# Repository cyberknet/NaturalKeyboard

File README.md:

# NaturalKeyboard
Custom Mechanical Keyboard PCB that will eventually have a Natural/Ergonomic layout. Never had PCBs fabricated, please reference or use at your own risk.

## Schematic

## PCB Front

## PCB Reverse

## Render Front

## Render Reverse

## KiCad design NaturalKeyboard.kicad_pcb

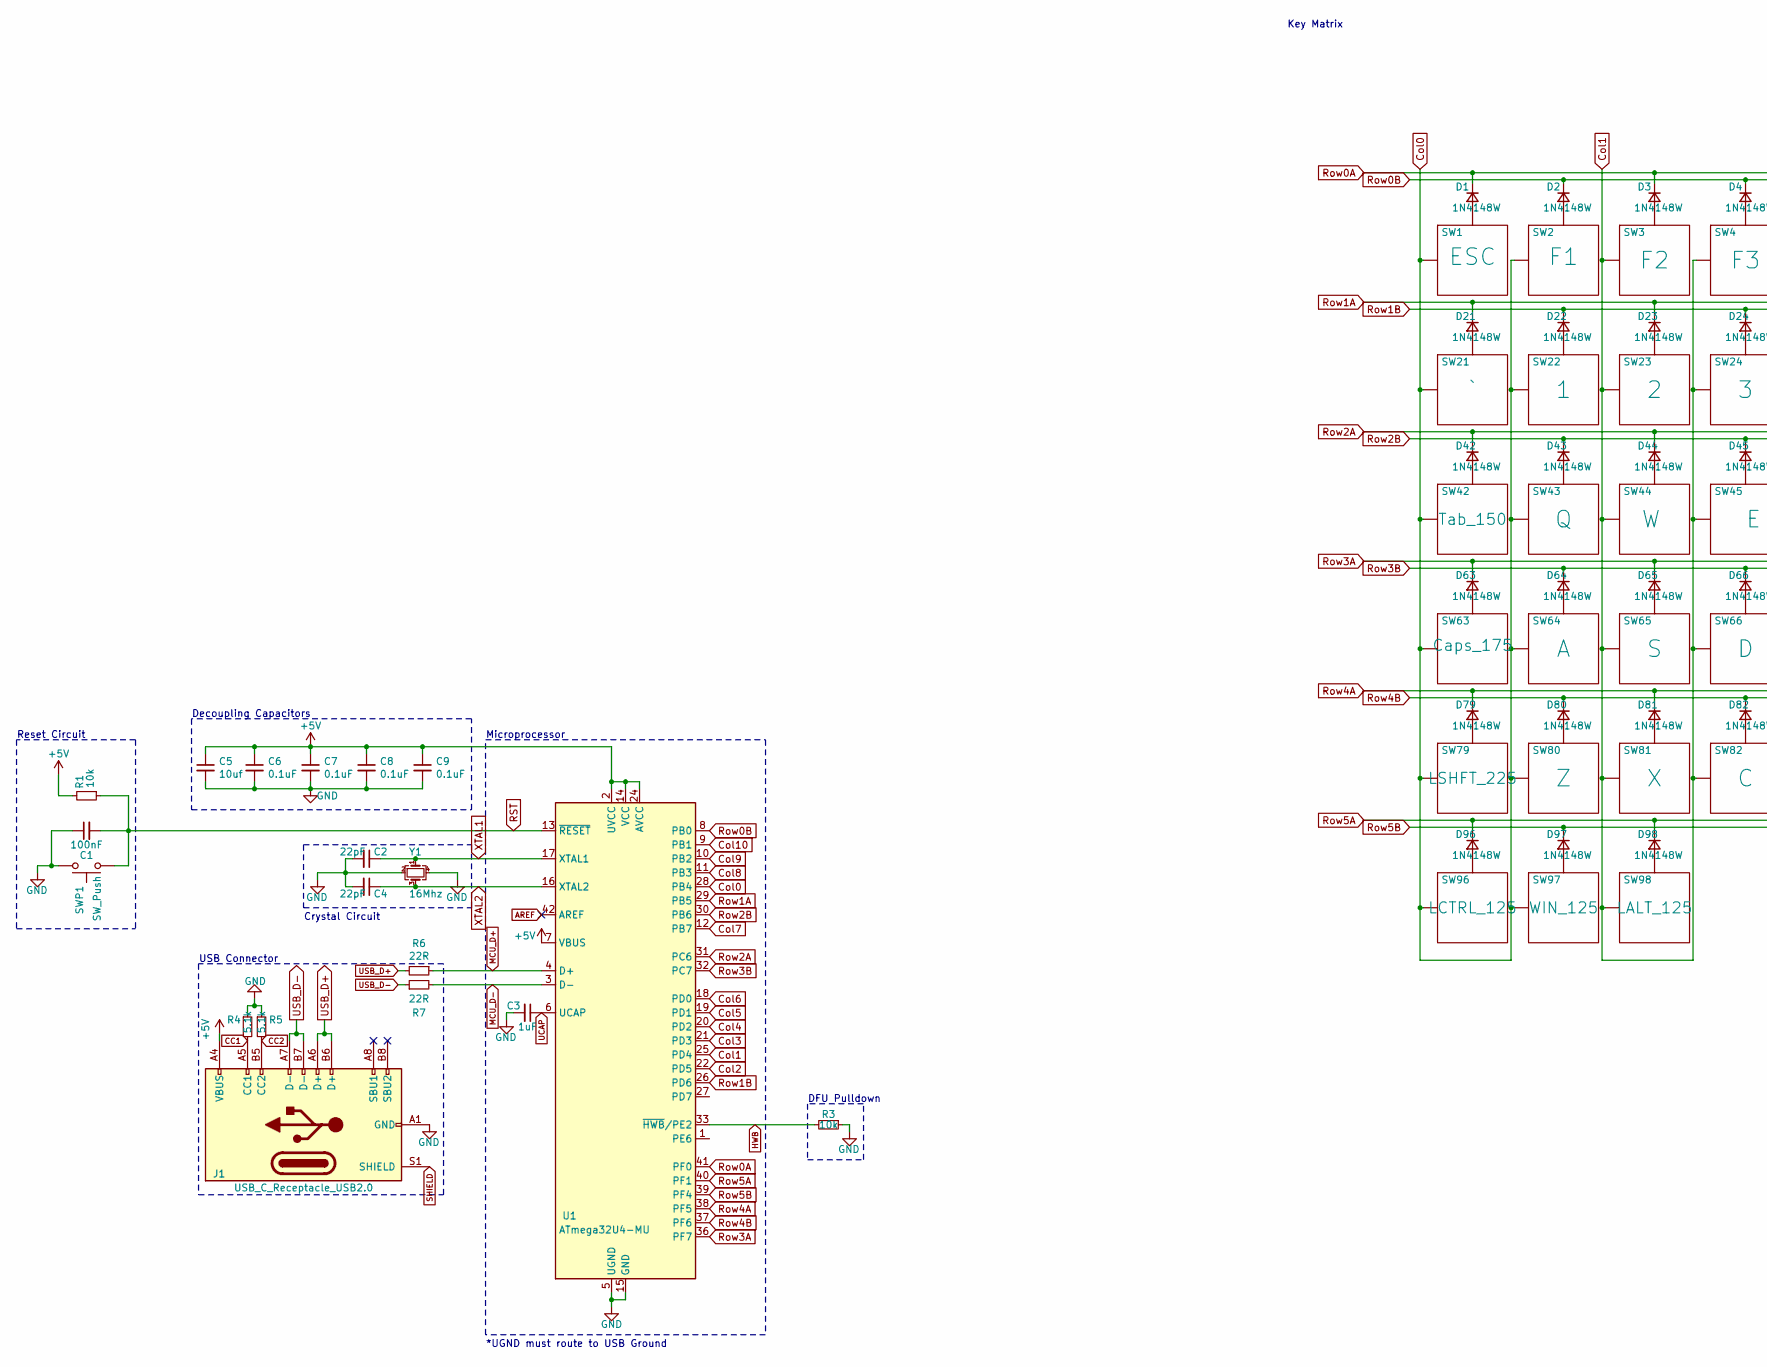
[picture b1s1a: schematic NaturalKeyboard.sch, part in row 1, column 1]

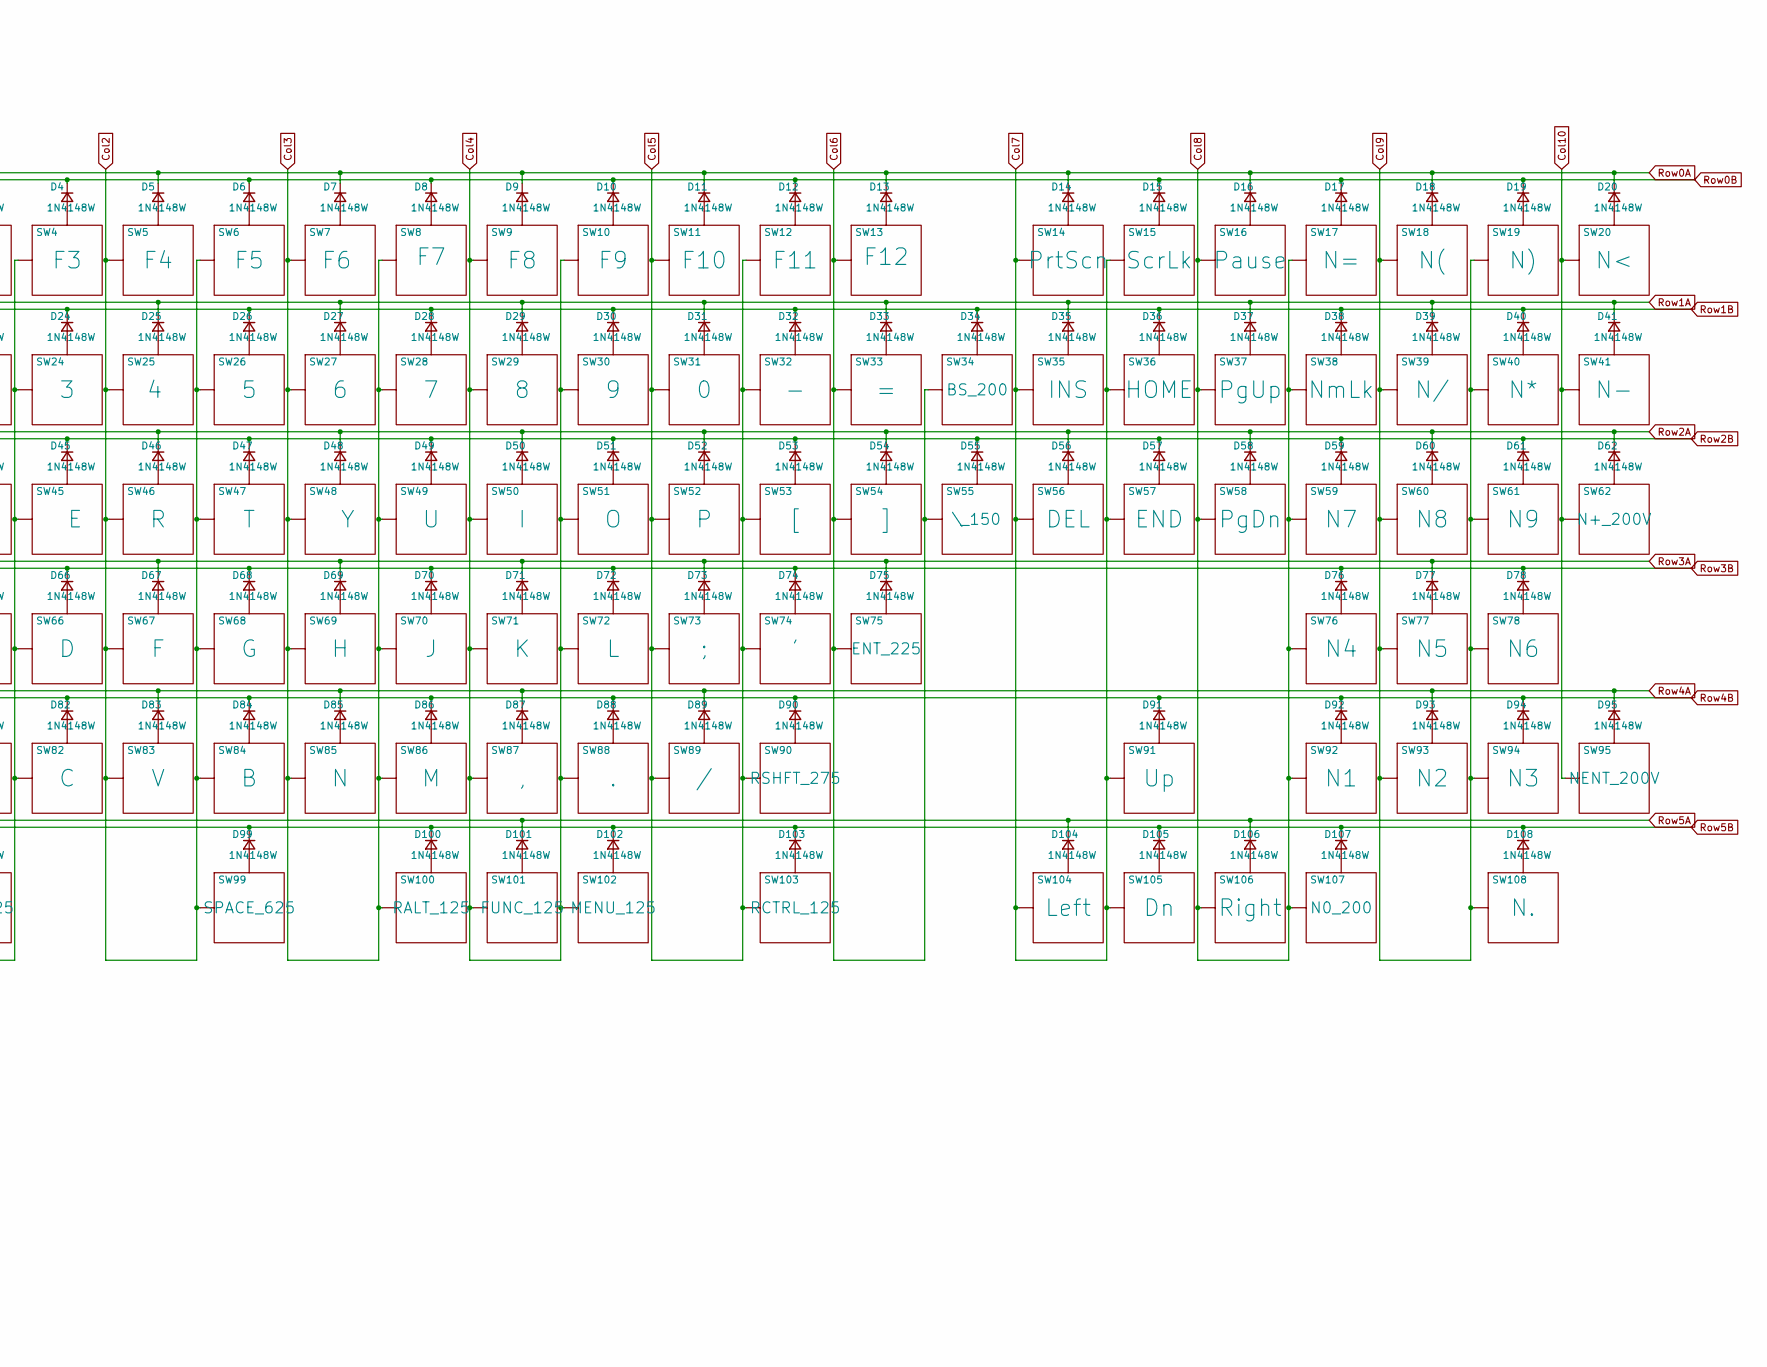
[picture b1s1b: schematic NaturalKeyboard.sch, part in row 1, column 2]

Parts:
C1: 100nF; C_0402_1005Metric
C2, C4: 22pF; C_0402_1005Metric
C3: 1uF; C_0402_1005Metric
C5: 10uf; C_0402_1005Metric
C6, C7, C8, C9: 0.1uF; C_0402_1005Metric
D1, D2, D3, D4, D5, D6, D7, D8, D9, D10, D11, D12, D13, D14, D15, D16, D17, D18, D19, D20, D21, D22, D23, D24, D25, D26, D27, D28, D29, D30, D31, D32, D33, D34, D35, D36, D37, D38, D39, D40, D41, D42, D43, D44, D45, D46, D47, D48, D49, D50, D51, D52, D53, D54, D55, D56, D57, D58, D59, D60, D61, D62, D63, D64, D65, D66, D67, D68, D69, D70, D71, D72, D73, D74, D75, D76, D77, D78, D79, D80, D81, D82, D83, D84, D85, D86, D87, D88, D89, D90, D91, D92, D93, D94, D95, D96, D97, D98, D99, D100, D101, D102, D103, D104, D105, D106, D107, D108: 1N4148W; D_SOD-123; PartNumber C81598
J1: USB_C_Receptacle_USB2.0; USB_C_Receptacle_HRO_TYPE-C-31-M-12; PartNumber C165948
R1, R3: 10k; R_0402_1005Metric
R4, R5: 5.1k; R_0402_1005Metric
R6, R7: 22R; R_0402_1005Metric
SW1: ESC; MX100
SW2: F1; MX100
SW3: F2; MX100
SW4: F3; MX100
SW5: F4; MX100
SW6: F5; MX100
SW7: F6; MX100
SW8: F7; MX100
SW9: F8; MX100
SW10: F9; MX100
SW11: F10; MX100
SW12: F11; MX100
SW13: F12; MX100
SW14: PrtScn; MX100
SW15: ScrLk; MX100
SW16: Pause; MX100
SW17: N=; MX100
SW18: N(; MX100
SW19: N); MX100
SW20: N<; MX100
SW21: `; MX100
SW22: 1; MX100
SW23: 2; MX100
SW24: 3; MX100
SW25: 4; MX100
SW26: 5; MX100
SW27: 6; MX100
SW28: 7; MX100
SW29: 8; MX100
SW30: 9; MX100
SW31: 0; MX100
SW32: -; MX100
SW33: =; MX100
SW34: BS_200; MX200
SW35: INS; MX100
SW36: HOME; MX100
SW37: PgUp; MX100
SW38: NmLk; MX100
SW39: N/; MX100
SW40: N*; MX100
SW41: N-; MX100
SW42: Tab_150; MX150
SW43: Q; MX100
SW44: W; MX100
SW45: E; MX100
SW46: R; MX100
SW47: T; MX100
SW48: Y; MX100
SW49: U; MX100
SW50: I; MX100
SW51: O; MX100
SW52: P; MX100
SW53: [; MX100
SW54: ]; MX100
SW55: \\_150; MX150
SW56: DEL; MX100
SW57: END; MX100
SW58: PgDn; MX100
SW59: N7; MX100
SW60: N8; MX100
SW61: N9; MX100
SW62: N+_200V; MX200V
SW63: Caps_175; MX175
SW64: A; MX100
SW65: S; MX100
SW66: D; MX100
SW67: F; MX100
SW68: G; MX100
SW69: H; MX100
SW70: J; MX100
SW71: K; MX100
SW72: L; MX100
SW73: ;; MX100
SW74: '; MX100
SW75: ENT_225; MX225
SW76: N4; MX100
SW77: N5; MX100
SW78: N6; MX100
SW79: LSHFT_225; MX225
SW80: Z; MX100
SW81: X; MX100
SW82: C; MX100
SW83: V; MX100
SW84: B; MX100
SW85: N; MX100
SW86: M; MX100
SW87: ,; MX100
SW88: .; MX100
SW89: /; MX100
SW90: RSHFT_275; MX275
SW91: Up; MX100
SW92: N1; MX100
SW93: N2; MX100
SW94: N3; MX100
SW95: NENT_200V; MX200V
SW96: LCTRL_125; MX125
SW97: WIN_125; MX125
SW98: LALT_125; MX125
SW99: SPACE_625; MX625
SW100: RALT_125; MX125
SW101: FUNC_125; MX125
SW102: MENU_125; MX125
SW103: RCTRL_125; MX125
SW104: Left; MX100
SW105: Dn; MX100
SW106: Right; MX100
SW107: N0_200; MX200
SW108: N.; MX100
SWP1: SW_Push; smdPushBtn
U1: ATmega32U4-MU; QFN-44-1EP_7x7mm_P0.5mm_EP5.2x5.2mm; PartNumber C45874
Y1: 16Mhz; Crystal_SMD_3225-4Pin_3.2x2.5mm; PartNumber C13738

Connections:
+5V: C5.1, C6.1, C7.1, C8.1, C9.1, J1.A4 (VBUS), J1.A9 (VBUS), J1.B4 (VBUS), J1.B9 (VBUS), R1.2, U1.2 (UVCC), U1.7 (VBUS), U1.14 (VCC), U1.24 (AVCC), U1.34 (VCC), U1.44 (AVCC)
AREF: U1.42 (AREF)
CC1: J1.A5 (CC1), R4.2
CC2: J1.B5 (CC2), R5.2
Col0: SW1.1 (Col), SW2.1 (Col), SW21.1 (Col), SW22.1 (Col), SW42.1 (Col), SW43.1 (Col), SW63.1 (Col), SW64.1 (Col), SW79.1 (Col), SW80.1 (Col), SW96.1 (Col), SW97.1 (Col), U1.28 (PB4)
Col1: SW3.1 (Col), SW4.1 (Col), SW23.1 (Col), SW24.1 (Col), SW44.1 (Col), SW45.1 (Col), SW65.1 (Col), SW66.1 (Col), SW81.1 (Col), SW82.1 (Col), SW98.1 (Col), U1.25 (PD4)
Col2: SW5.1 (Col), SW6.1 (Col), SW25.1 (Col), SW26.1 (Col), SW46.1 (Col), SW47.1 (Col), SW67.1 (Col), SW68.1 (Col), SW83.1 (Col), SW84.1 (Col), SW99.1 (Col), U1.22 (PD5)
Col3: SW7.1 (Col), SW8.1 (Col), SW27.1 (Col), SW28.1 (Col), SW48.1 (Col), SW49.1 (Col), SW69.1 (Col), SW70.1 (Col), SW85.1 (Col), SW86.1 (Col), SW100.1 (Col), U1.21 (PD3)
Col4: SW9.1 (Col), SW10.1 (Col), SW29.1 (Col), SW30.1 (Col), SW50.1 (Col), SW51.1 (Col), SW71.1 (Col), SW72.1 (Col), SW87.1 (Col), SW88.1 (Col), SW101.1 (Col), SW102.1 (Col), U1.20 (PD2)
Col5: SW11.1 (Col), SW12.1 (Col), SW31.1 (Col), SW32.1 (Col), SW52.1 (Col), SW53.1 (Col), SW73.1 (Col), SW74.1 (Col), SW89.1 (Col), SW90.1 (Col), SW103.1 (Col), U1.19 (PD1)
Col6: SW13.1 (Col), SW33.1 (Col), SW34.1 (Col), SW54.1 (Col), SW55.1 (Col), SW75.1 (Col), U1.18 (PD0)
Col7: SW14.1 (Col), SW15.1 (Col), SW35.1 (Col), SW36.1 (Col), SW56.1 (Col), SW57.1 (Col), SW91.1 (Col), SW104.1 (Col), SW105.1 (Col), U1.12 (PB7)
Col8: SW16.1 (Col), SW17.1 (Col), SW37.1 (Col), SW38.1 (Col), SW58.1 (Col), SW59.1 (Col), SW76.1 (Col), SW92.1 (Col), SW106.1 (Col), SW107.1 (Col), U1.11 (PB3)
Col9: SW18.1 (Col), SW19.1 (Col), SW39.1 (Col), SW40.1 (Col), SW60.1 (Col), SW61.1 (Col), SW77.1 (Col), SW78.1 (Col), SW93.1 (Col), SW94.1 (Col), SW108.1 (Col), U1.10 (PB2)
Col10: SW20.1 (Col), SW41.1 (Col), SW62.1 (Col), SW95.1 (Col), U1.9 (PB1)
GND: C1.1, C2.2, C3.2, C4.2, C5.2, C6.2, C7.2, C8.2, C9.2, J1.A1 (GND), J1.A12 (GND), J1.B1 (GND), J1.B12 (GND), R3.1, R4.1, R5.1, SWP1.2, U1.5 (UGND), U1.15 (GND), U1.23 (GND), U1.35 (GND), U1.43 (GND), U1.45 (GND), Y1.2, Y1.4
HWB: R3.2, U1.33 (~HWB~/PE2)
MCU_D+: R6.1, U1.4 (D+)
MCU_D-: R7.2, U1.3 (D-)
unnamed: D1.2 (A), SW1.2 (Row)
unnamed: D2.2 (A), SW2.2 (Row)
unnamed: D3.2 (A), SW3.2 (Row)
unnamed: D4.2 (A), SW4.2 (Row)
unnamed: D5.2 (A), SW5.2 (Row)
unnamed: D6.2 (A), SW6.2 (Row)
unnamed: D7.2 (A), SW7.2 (Row)
unnamed: D8.2 (A), SW8.2 (Row)
unnamed: D9.2 (A), SW9.2 (Row)
unnamed: D10.2 (A), SW10.2 (Row)
unnamed: D11.2 (A), SW11.2 (Row)
unnamed: D12.2 (A), SW12.2 (Row)
unnamed: D13.2 (A), SW13.2 (Row)
unnamed: D14.2 (A), SW14.2 (Row)
unnamed: D15.2 (A), SW15.2 (Row)
unnamed: D16.2 (A), SW16.2 (Row)
unnamed: D17.2 (A), SW17.2 (Row)
unnamed: D18.2 (A), SW18.2 (Row)
unnamed: D19.2 (A), SW19.2 (Row)
unnamed: D20.2 (A), SW20.2 (Row)
unnamed: D21.2 (A), SW21.2 (Row)
unnamed: D22.2 (A), SW22.2 (Row)
unnamed: D23.2 (A), SW23.2 (Row)
unnamed: D24.2 (A), SW24.2 (Row)
unnamed: D25.2 (A), SW25.2 (Row)
unnamed: D26.2 (A), SW26.2 (Row)
unnamed: D27.2 (A), SW27.2 (Row)
unnamed: D28.2 (A), SW28.2 (Row)
unnamed: D29.2 (A), SW29.2 (Row)
unnamed: D30.2 (A), SW30.2 (Row)
unnamed: D31.2 (A), SW31.2 (Row)
unnamed: D32.2 (A), SW32.2 (Row)
unnamed: D33.2 (A), SW33.2 (Row)
unnamed: D34.2 (A), SW34.2 (Row)
unnamed: D35.2 (A), SW35.2 (Row)
unnamed: D36.2 (A), SW36.2 (Row)
unnamed: D37.2 (A), SW37.2 (Row)
unnamed: D38.2 (A), SW38.2 (Row)
unnamed: D39.2 (A), SW39.2 (Row)
unnamed: D40.2 (A), SW40.2 (Row)
unnamed: D41.2 (A), SW41.2 (Row)
unnamed: D42.2 (A), SW42.2 (Row)
unnamed: D43.2 (A), SW43.2 (Row)
unnamed: D44.2 (A), SW44.2 (Row)
unnamed: D45.2 (A), SW45.2 (Row)
unnamed: D46.2 (A), SW46.2 (Row)
unnamed: D47.2 (A), SW47.2 (Row)
unnamed: D48.2 (A), SW48.2 (Row)
unnamed: D49.2 (A), SW49.2 (Row)
unnamed: D50.2 (A), SW50.2 (Row)
unnamed: D51.2 (A), SW51.2 (Row)
unnamed: D52.2 (A), SW52.2 (Row)
unnamed: D53.2 (A), SW53.2 (Row)
unnamed: D54.2 (A), SW54.2 (Row)
unnamed: D55.2 (A), SW55.2 (Row)
unnamed: D56.2 (A), SW56.2 (Row)
unnamed: D57.2 (A), SW57.2 (Row)
unnamed: D58.2 (A), SW58.2 (Row)
unnamed: D59.2 (A), SW59.2 (Row)
unnamed: D60.2 (A), SW60.2 (Row)
unnamed: D61.2 (A), SW61.2 (Row)
unnamed: D62.2 (A), SW62.2 (Row)
unnamed: D63.2 (A), SW63.2 (Row)
unnamed: D64.2 (A), SW64.2 (Row)
unnamed: D65.2 (A), SW65.2 (Row)
unnamed: D66.2 (A), SW66.2 (Row)
unnamed: D67.2 (A), SW67.2 (Row)
unnamed: D68.2 (A), SW68.2 (Row)
unnamed: D69.2 (A), SW69.2 (Row)
unnamed: D70.2 (A), SW70.2 (Row)
unnamed: D71.2 (A), SW71.2 (Row)
unnamed: D72.2 (A), SW72.2 (Row)
unnamed: D73.2 (A), SW73.2 (Row)
unnamed: D74.2 (A), SW74.2 (Row)
unnamed: D75.2 (A), SW75.2 (Row)
unnamed: D76.2 (A), SW76.2 (Row)
unnamed: D77.2 (A), SW77.2 (Row)
unnamed: D78.2 (A), SW78.2 (Row)
unnamed: D79.2 (A), SW79.2 (Row)
unnamed: D80.2 (A), SW80.2 (Row)
unnamed: D81.2 (A), SW81.2 (Row)
unnamed: D82.2 (A), SW82.2 (Row)
unnamed: D83.2 (A), SW83.2 (Row)
unnamed: D84.2 (A), SW84.2 (Row)
unnamed: D85.2 (A), SW85.2 (Row)
unnamed: D86.2 (A), SW86.2 (Row)
unnamed: D87.2 (A), SW87.2 (Row)
unnamed: D88.2 (A), SW88.2 (Row)
unnamed: D89.2 (A), SW89.2 (Row)
unnamed: D90.2 (A), SW90.2 (Row)
unnamed: D91.2 (A), SW91.2 (Row)
unnamed: D92.2 (A), SW92.2 (Row)
unnamed: D93.2 (A), SW93.2 (Row)
unnamed: D94.2 (A), SW94.2 (Row)
unnamed: D95.2 (A), SW95.2 (Row)
unnamed: D96.2 (A), SW96.2 (Row)
unnamed: D97.2 (A), SW97.2 (Row)
unnamed: D98.2 (A), SW98.2 (Row)
unnamed: D99.2 (A), SW99.2 (Row)
unnamed: D100.2 (A), SW100.2 (Row)
unnamed: D101.2 (A), SW101.2 (Row)
unnamed: D102.2 (A), SW102.2 (Row)
unnamed: D103.2 (A), SW103.2 (Row)
unnamed: D104.2 (A), SW104.2 (Row)
unnamed: D105.2 (A), SW105.2 (Row)
unnamed: D106.2 (A), SW106.2 (Row)
unnamed: D107.2 (A), SW107.2 (Row)
unnamed: D108.2 (A), SW108.2 (Row)
RST: C1.2, R1.1, SWP1.1, U1.13 (~RESET)
Row0A: D1.1 (K), D3.1 (K), D5.1 (K), D7.1 (K), D9.1 (K), D11.1 (K), D13.1 (K), D14.1 (K), D16.1 (K), D18.1 (K), D20.1 (K), U1.41 (PF0)
Row0B: D2.1 (K), D4.1 (K), D6.1 (K), D8.1 (K), D10.1 (K), D12.1 (K), D15.1 (K), D17.1 (K), D19.1 (K), U1.8 (PB0)
Row1A: D21.1 (K), D23.1 (K), D25.1 (K), D27.1 (K), D29.1 (K), D31.1 (K), D33.1 (K), D35.1 (K), D37.1 (K), D39.1 (K), D41.1 (K), U1.29 (PB5)
Row1B: D22.1 (K), D24.1 (K), D26.1 (K), D28.1 (K), D30.1 (K), D32.1 (K), D34.1 (K), D36.1 (K), D38.1 (K), D40.1 (K), U1.26 (PD6)
Row2A: D42.1 (K), D44.1 (K), D46.1 (K), D48.1 (K), D50.1 (K), D52.1 (K), D54.1 (K), D56.1 (K), D58.1 (K), D60.1 (K), D62.1 (K), U1.31 (PC6)
Row2B: D43.1 (K), D45.1 (K), D47.1 (K), D49.1 (K), D51.1 (K), D53.1 (K), D55.1 (K), D57.1 (K), D59.1 (K), D61.1 (K), U1.30 (PB6)
Row3A: D63.1 (K), D65.1 (K), D67.1 (K), D69.1 (K), D71.1 (K), D73.1 (K), D75.1 (K), D77.1 (K), U1.36 (PF7)
Row3B: D64.1 (K), D66.1 (K), D68.1 (K), D70.1 (K), D72.1 (K), D74.1 (K), D76.1 (K), D78.1 (K), U1.32 (PC7)
Row4A: D79.1 (K), D81.1 (K), D83.1 (K), D85.1 (K), D87.1 (K), D89.1 (K), D93.1 (K), D95.1 (K), U1.38 (PF5)
Row4B: D80.1 (K), D82.1 (K), D84.1 (K), D86.1 (K), D88.1 (K), D90.1 (K), D91.1 (K), D92.1 (K), D94.1 (K), U1.37 (PF6)
Row5A: D96.1 (K), D98.1 (K), D101.1 (K), D104.1 (K), D106.1 (K), U1.40 (PF1)
Row5B: D97.1 (K), D99.1 (K), D100.1 (K), D102.1 (K), D103.1 (K), D105.1 (K), D107.1 (K), D108.1 (K), U1.39 (PF4)
SHIELD: J1.S1 (SHIELD)
UCAP: C3.1, U1.6 (UCAP)
USB_D+: J1.A6 (D+), J1.B6 (D+), R6.2
USB_D-: J1.A7 (D-), J1.B7 (D-), R7.1
XTAL1: C2.1, U1.17 (XTAL1), Y1.1
XTAL2: C4.1, U1.16 (XTAL2), Y1.3

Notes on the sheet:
Reset Circuit
Decoupling Capacitors
USB Connector
Microprocessor
Key Matrix
Crystal Circuit
DFU Pulldown
*UGND must route to USB Ground

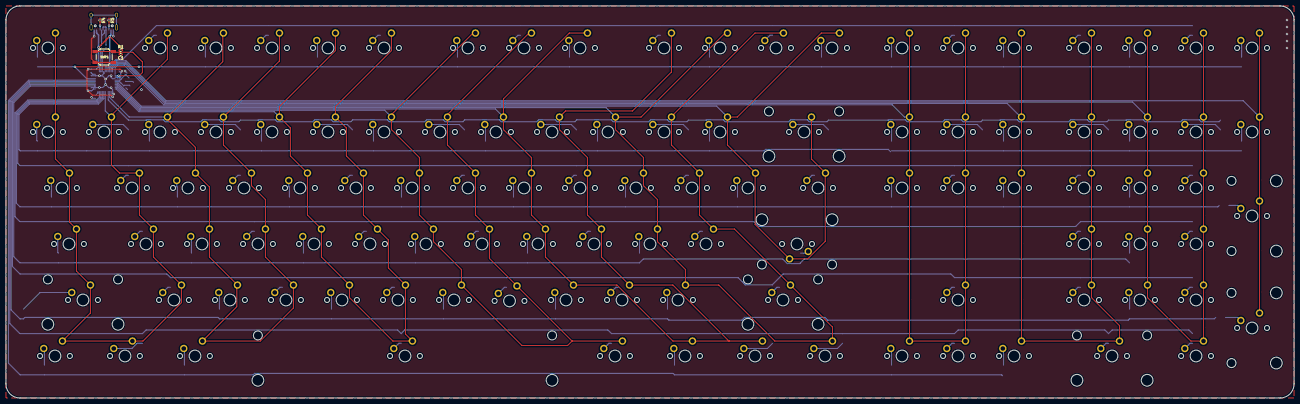
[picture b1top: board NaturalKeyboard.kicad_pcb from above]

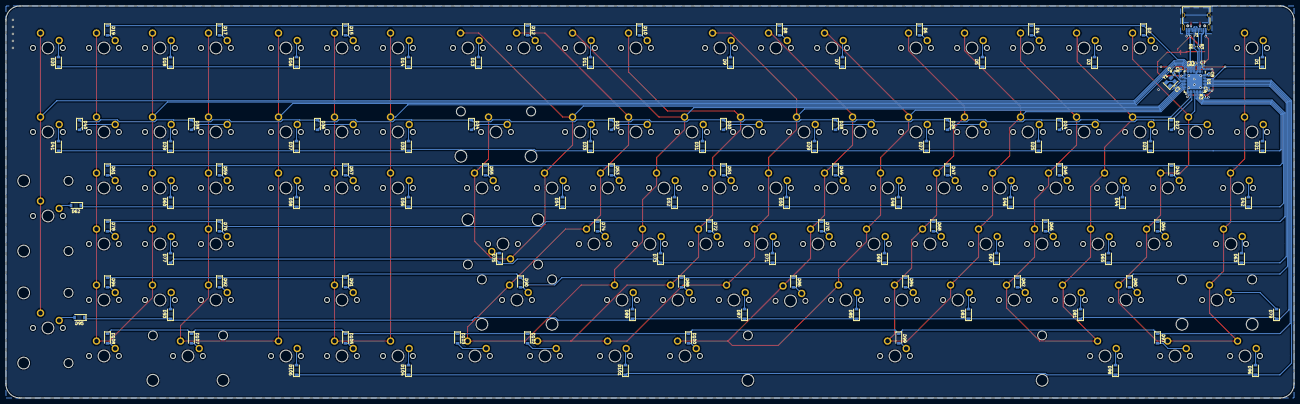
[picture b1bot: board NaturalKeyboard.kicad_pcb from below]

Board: 2 copper layers, 438.1 x 133.3 mm, 235 parts (230 on the bottom side), 144 nets.

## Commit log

2020-10-18 Start tracking KiCAD changes
2020-10-20 PCB Review Time!
2020-10-20 Added preview images
2020-10-20 Commit schematic after export PNG
2020-10-20 Added Board Renders
2020-10-20 Update README.md
    Fixed the bad links in the README.md
